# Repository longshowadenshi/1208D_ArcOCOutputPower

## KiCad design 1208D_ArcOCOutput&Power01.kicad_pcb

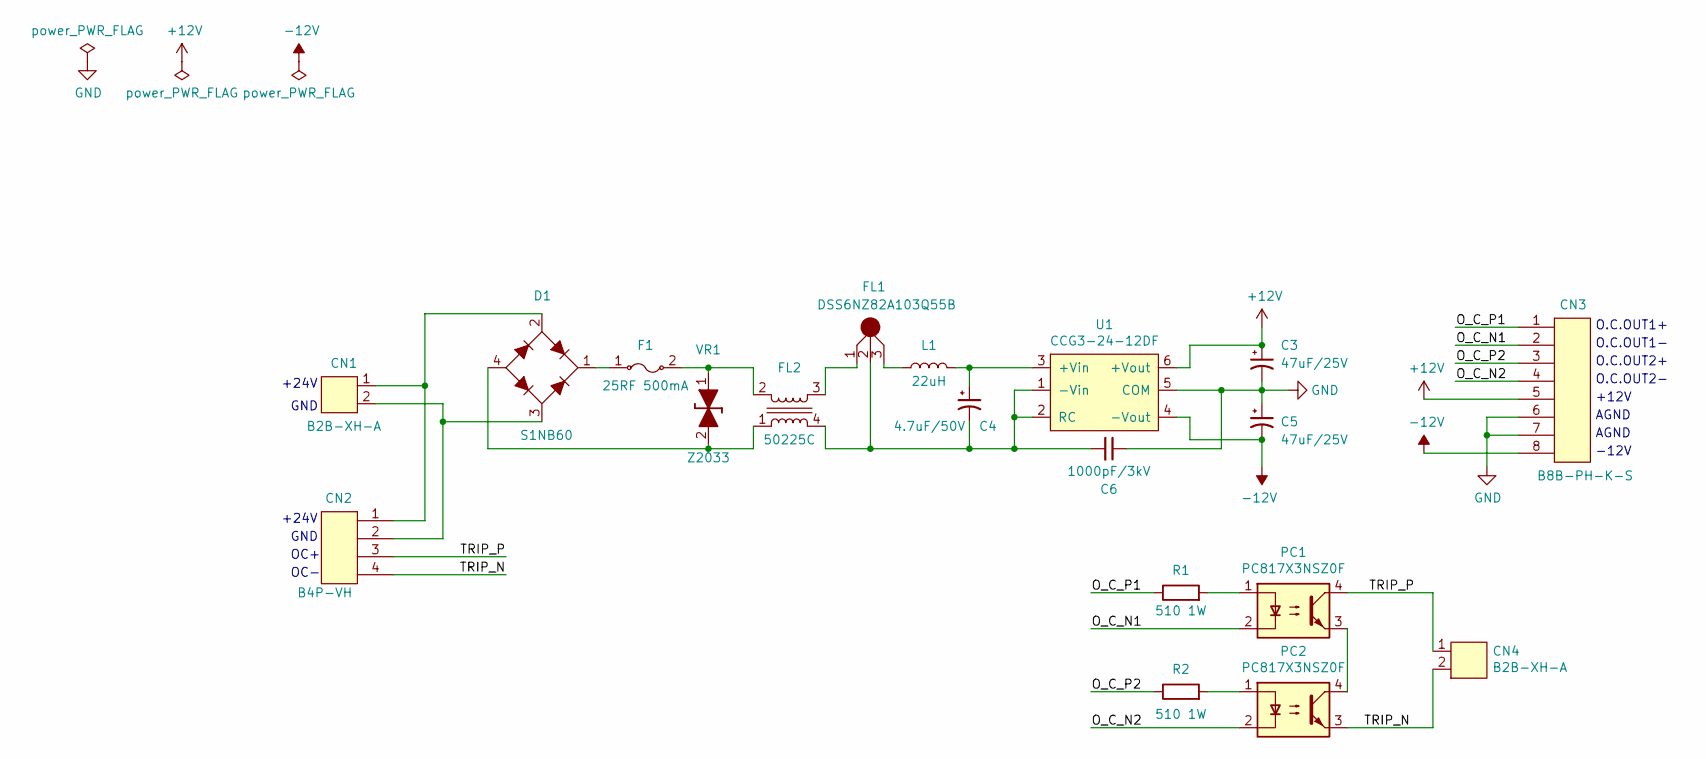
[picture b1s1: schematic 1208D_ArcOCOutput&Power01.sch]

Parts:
C3, C5: 47uF/25V; 10uF-16v
C4: 4.7uF/50V; 10uF-16v
C6: 1000pF/3kV; CK45-R3FD102K-NRA
CN1, CN4: B2B-XH-A; XH-2pins
CN2: B4P-VH; cn_B4P-VH
CN3: B8B-PH-K-S; cn_B8B-PH-K-S
D1: S1NB60; DiodeBrigde
F1: 25RF 500mA; 25RF-500mA
FL1: DSS6NZ82A103Q55B
FL2: 50225C
L1: 22uH; TSL0709RA-220K1R3
PC1, PC2: PC817X3NSZ0F
R1, R2: 510 1W; RK73-2512
U1: CCG3-24-12DF
VR1: Z2033; z2033

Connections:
+12V: C3.1, CN3.5, U1.6 (+Vout)
-12V: C5.2, CN3.8, U1.4 (-Vout)
/O_C_N1: CN3.2, PC1.2
/O_C_N2: CN3.4, PC2.2
/O_C_P1: CN3.1, R1.1
/O_C_P2: CN3.3, R2.1
/TRIP_N: CN2.4, CN4.2, PC2.3
/TRIP_P: CN2.3, CN4.1, PC1.4
GND: C3.2, C5.1, C6.1, CN3.6, CN3.7, U1.5 (COM)
unnamed: C4.1, L1.2, U1.3 (+Vin)
unnamed: C4.2, C6.2, FL1.2, FL2.4, U1.1 (-Vin), U1.2 (RC)
unnamed: CN1.1, CN2.1, D1.2
unnamed: CN1.2, CN2.2, D1.3
unnamed: D1.1, F1.1
unnamed: D1.4, FL2.1, VR1.2
unnamed: F1.2, FL2.2, VR1.1
unnamed: FL1.1, FL2.3
unnamed: FL1.3, L1.1
unnamed: PC1.1, R1.2
unnamed: PC1.3, PC2.4
unnamed: PC2.1, R2.2

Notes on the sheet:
+24V
GND
OC+
OC-
O.C.OUT1+
O.C.OUT1-
O.C.OUT2+
O.C.OUT2-
+12V
AGND
-12V

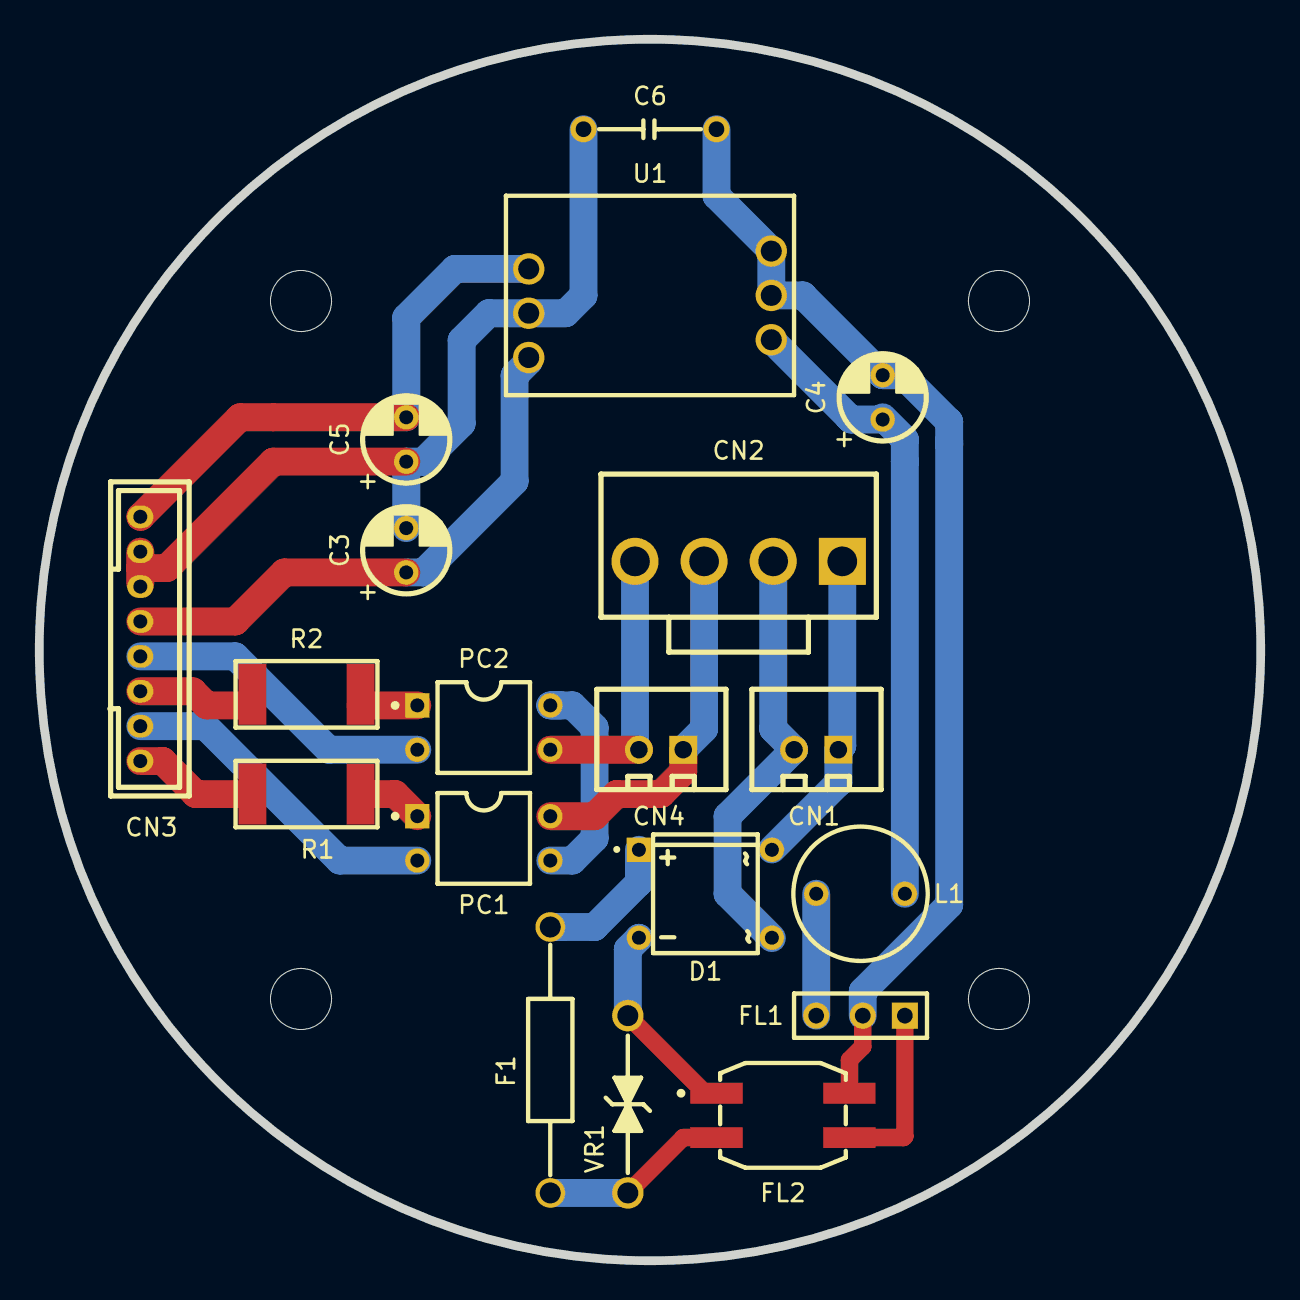
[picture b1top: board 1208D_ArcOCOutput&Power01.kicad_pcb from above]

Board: 2 copper layers, 70.0 x 70.0 mm, 19 parts (0 on the bottom side), 21 nets.
